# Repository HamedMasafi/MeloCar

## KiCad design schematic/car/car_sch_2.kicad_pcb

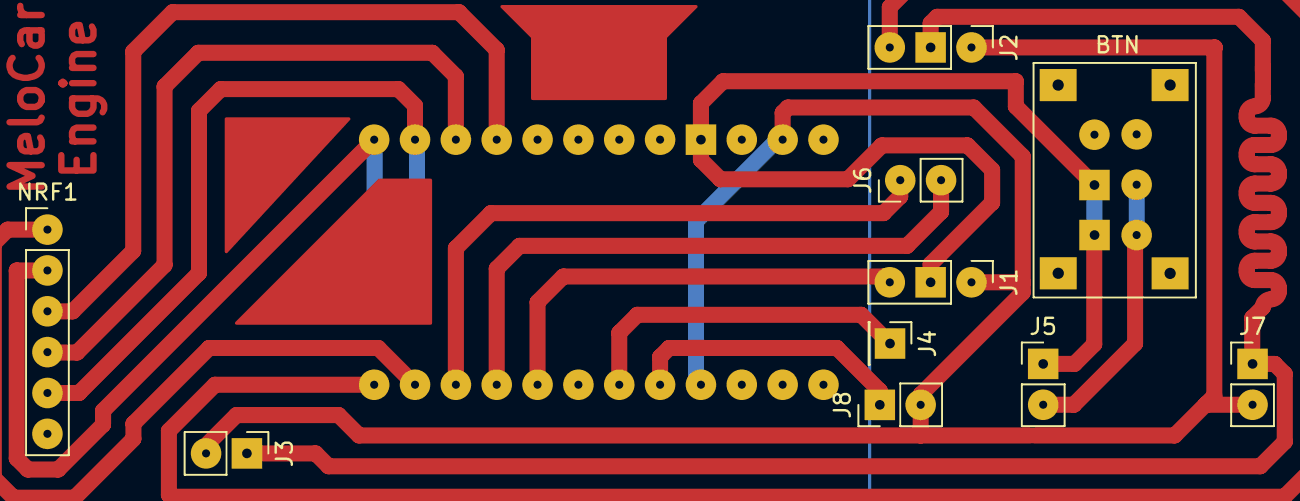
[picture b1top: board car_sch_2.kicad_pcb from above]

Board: 2 copper layers, 11 parts (1 on the bottom side), 13 nets.

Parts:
BTN: Power_btn; PushButton_6_pin
J1: Led (D+-); PinHeader_1x03_P2.54mm_Vertical
J2: Servo (D+-); PinHeader_1x03_P2.54mm_Vertical
J3: NRF_Power; PinHeader_1x02_P2.54mm_Vertical
J4: Accel; PinHeader_1x01_P2.54mm_Vertical
J5: Micro-Power-IN; PinHeader_1x02_P2.54mm_Vertical
J6: MOTOR-CTRL; PinHeader_1x02_P2.54mm_Vertical
J7: MOTOR-PWR-OUT; PinHeader_1x02_P2.54mm_Vertical
J8: Horn (+-); PinHeader_1x02_P2.54mm_Vertical
NRF1: NRF24L01; PinHeader_1x06_P2.54mm_Vertical
U1: ARDUINO_PRO_MINI; MODULE_ARDUINO_PRO_MINI

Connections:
+5V: BTN.3, BTN.5, J1.2, J2.2, J3.1, J5.1, J7.1, U1.JP6_4 (VCC_1)
GND: BTN.4, BTN.6, J1.1, J2.1, J3.2, J5.2, J7.2, J8.2, U1.JP6_2 (GND_1), U1.JP7_9 (GND_2)
unnamed: J1.3, U1.JP7_5 (D5)
unnamed: J2.3, U1.JP7_1 (D9)
unnamed: J4.1, U1.JP7_7 (D3)
unnamed: J6.2, U1.JP7_4 (D6)
unnamed: J8.1, U1.JP7_8 (D2)
unnamed: NRF1.1, U1.JP7_2 (D8)
unnamed: NRF1.2, U1.JP6_12 (D10)
unnamed: NRF1.3, U1.JP6_9 (SCK)
unnamed: NRF1.4, U1.JP6_10 (MISO)
unnamed: NRF1.5, U1.JP6_11 (MOSI)
unnamed: J6.1, U1.JP7_3 (D7)

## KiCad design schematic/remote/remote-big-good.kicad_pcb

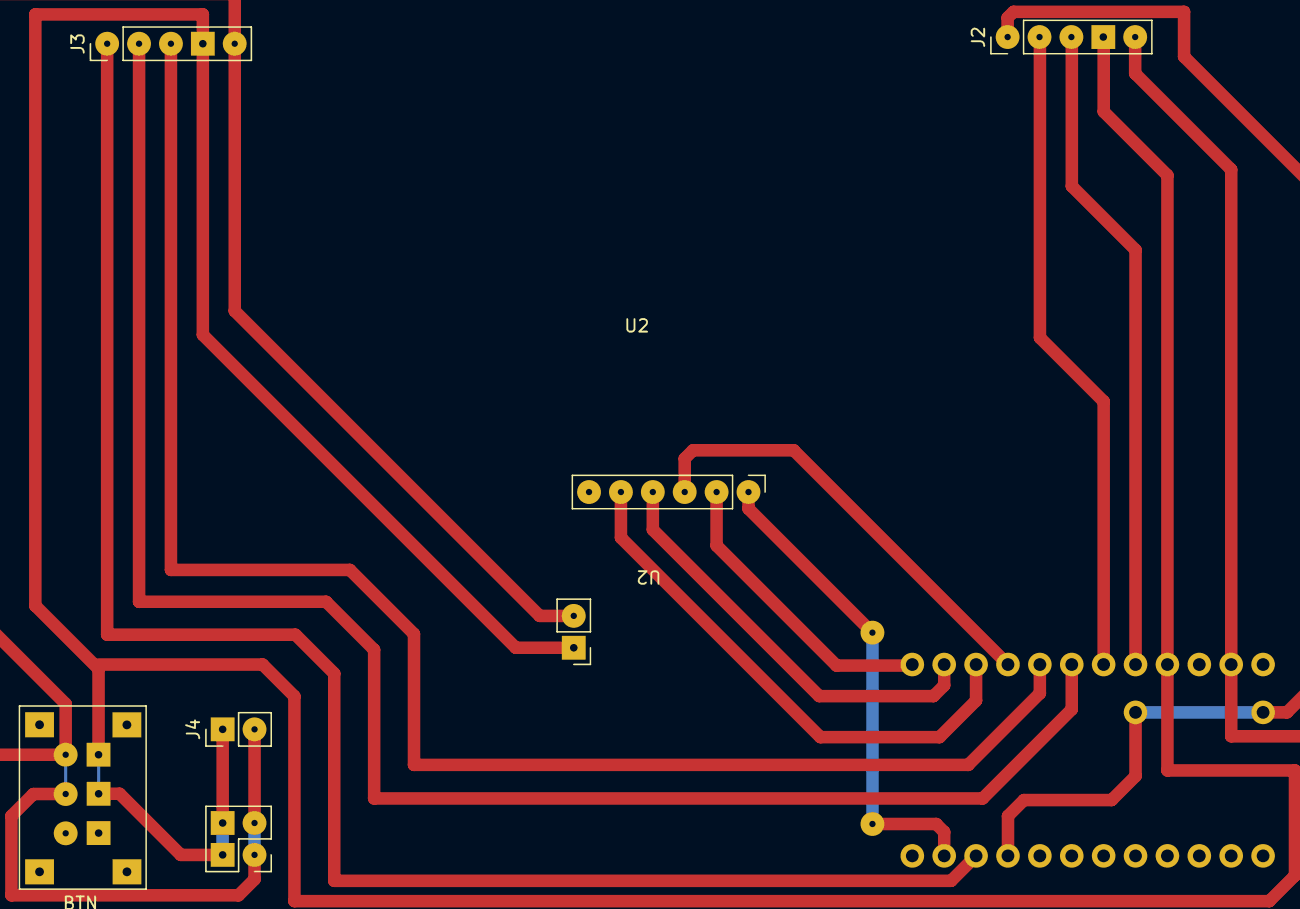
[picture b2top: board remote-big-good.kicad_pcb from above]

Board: 2 copper layers, 6 parts (1 on the bottom side), 13 nets.

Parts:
BTN: PushButton_6_pin
J2: Joystick_Left; PinHeader_1x05_P2.54mm_Vertical
J3: Joystick_Right; PinHeader_1x05_P2.54mm_Vertical
J4: Micro-Power-IN; PinHeader_1x02_P2.54mm_Vertical
U1: ARDUINO_PRO_MINI; MODULE_ARDUINO_PRO_MINI
U2: NRF24L01_Breakout; NRF24L01

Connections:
+5V: BTN.3, BTN.5, J2.4, J3.4, J4.1, U1.JP6_4 (VCC_1), U2.2 (VCC)
GND: BTN.4, BTN.6, J2.5, J3.5, J4.2, U1.JP6_2 (GND_1), U2.1 (GND)
unnamed: J2.1, U1.JP7_4 (D6)
unnamed: J2.2, U1.JP6_6 (A2)
unnamed: J2.3, U1.JP6_5 (A3)
unnamed: J3.1, U1.JP7_3 (D7)
unnamed: J3.2, U1.JP6_7 (A1)
unnamed: J3.3, U1.JP6_8 (A0)
unnamed: U1.JP6_9 (SCK), U2.5 (SCK)
unnamed: U1.JP6_10 (MISO), U2.7 (MISO)
unnamed: U1.JP6_11 (MOSI), U2.6 (MOSI)
unnamed: U1.JP6_12 (D10), U2.4 (~CSN)
unnamed: U1.JP7_2 (D8), U2.3 (CE)
